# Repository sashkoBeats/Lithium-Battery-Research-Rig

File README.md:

# Lithium Battery Research Rig
University project development of a rig for 18650 lithium battery testing and research.   
End goal is an EV simulation rig for researching EV battery health and performance.   
Created by Aleksandar Zdravkov and Indra Erkens   
Fontys University of Applied Sciences   
S7 Project and CSA1/2 2022-2024

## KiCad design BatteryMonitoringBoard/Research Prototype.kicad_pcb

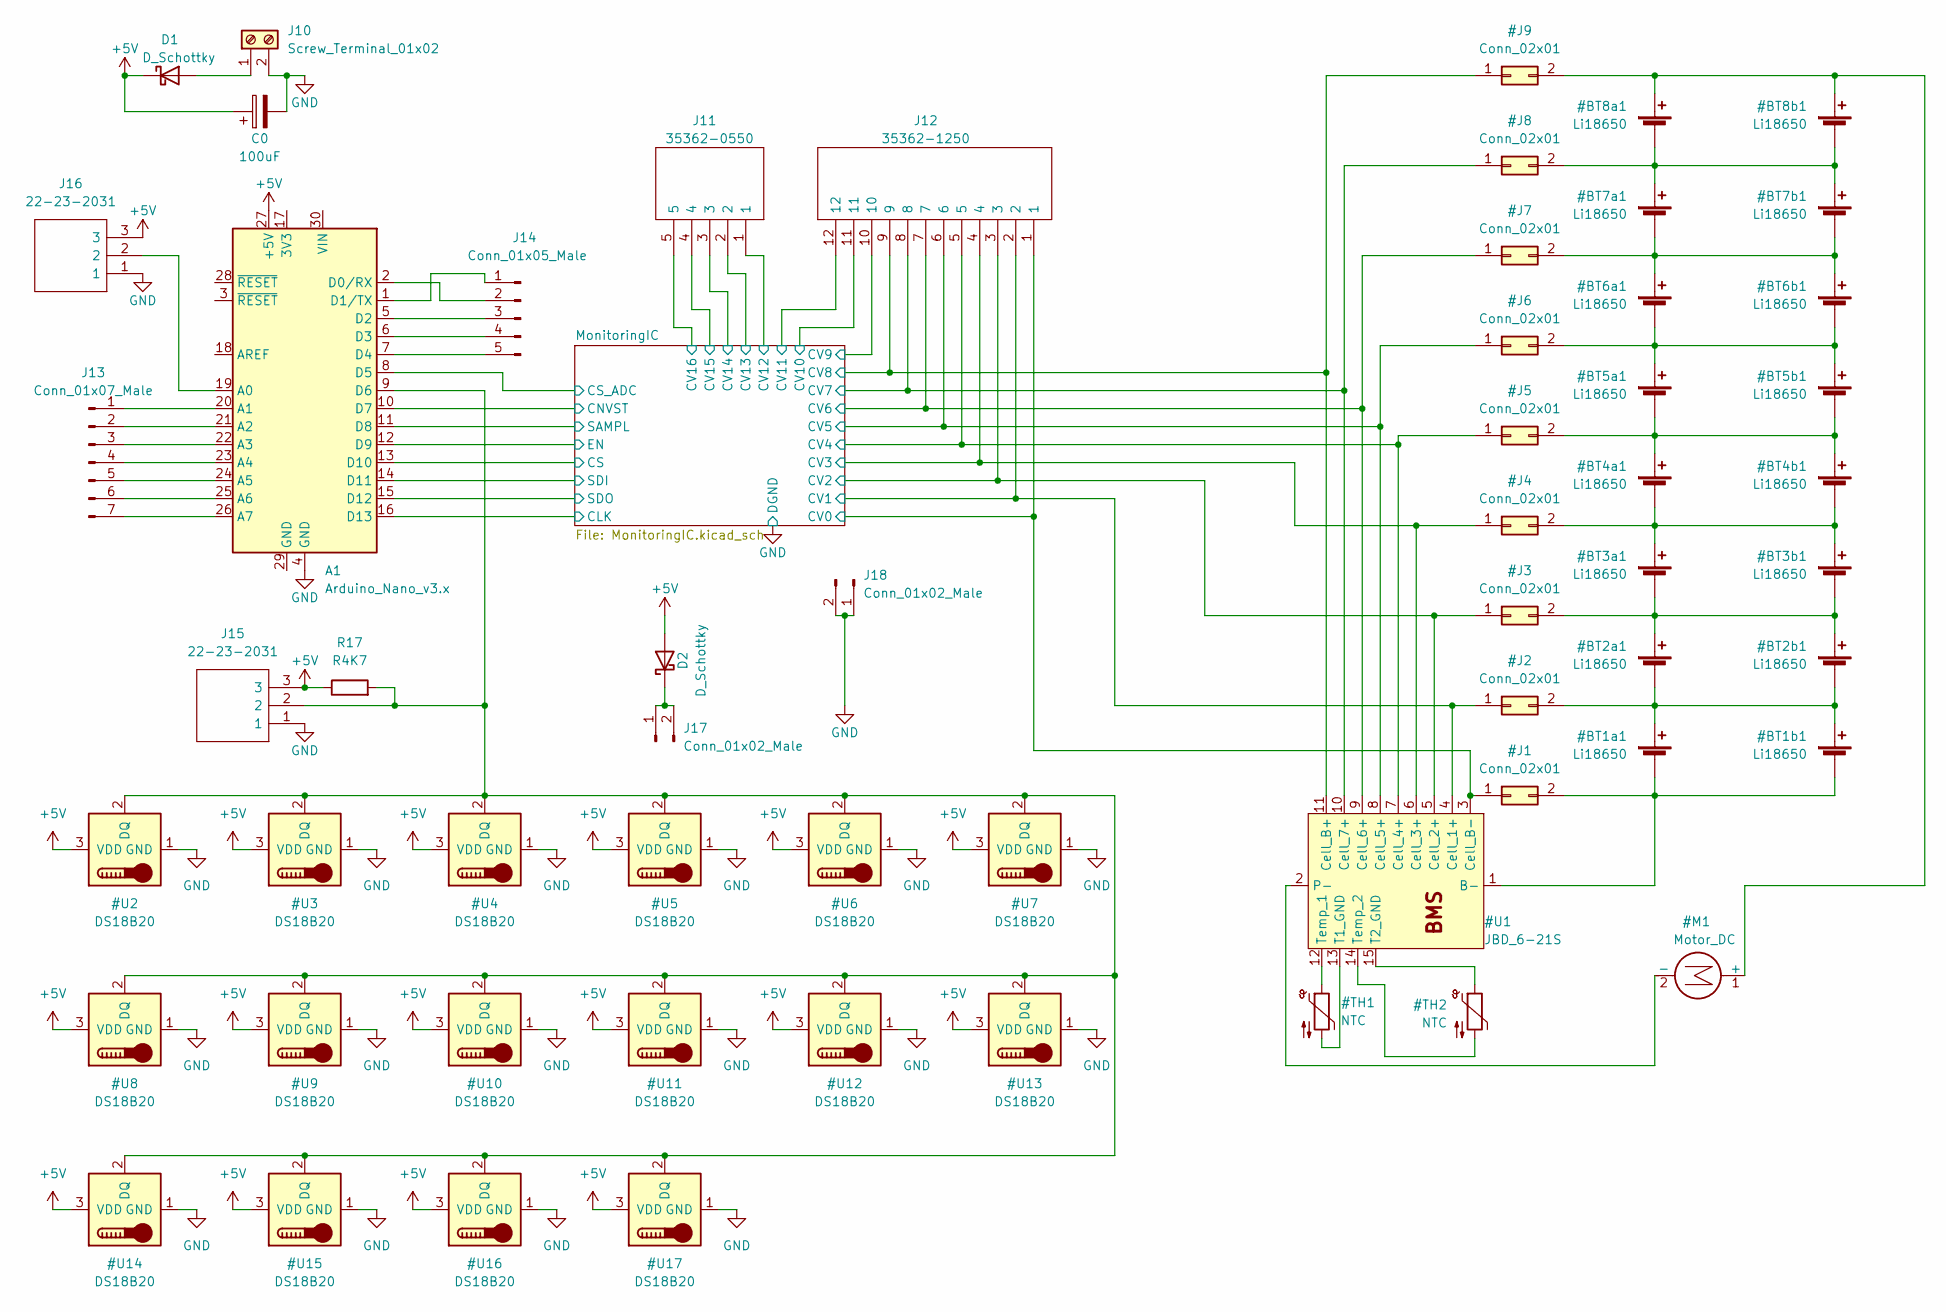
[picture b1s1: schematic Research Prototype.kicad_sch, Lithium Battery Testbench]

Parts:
A1: Arduino_Nano_v3.x; Arduino_Nano
C0: 100uF; CAPPRD250W50D680H1250
D1, D2: D_Schottky; SOD2512X115N
J10: Screw_Terminal_01x02; TerminalBlock_bornier-2_P5.08mm
J11: 35362-0550; SHDR5W50P0X200_1X5_1230X550X850P; Manufacturer_Part_Number 35362-0550; Mouser Part Number 538-35362-0550
J12: 35362-1250; 353621250; Manufacturer_Part_Number 35362-1250; Mouser Part Number 538-35362-1250
J13: Conn_01x07_Male; PinHeader_1x07_P2.54mm_Vertical
J14: Conn_01x05_Male
J15, J16: 22-23-2031; SHDR3W82P0X254_1X3_747X635X818P; Manufacturer_Part_Number 22-23-2031; Mouser Part Number 538-22-23-2031
J17, J18: Conn_01x02_Male; PinHeader_1x02_P2.54mm_Vertical
R17: R4K7; R_Axial_DIN0309_L9.0mm_D3.2mm_P12.70mm_Horizontal

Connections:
/MonitoringIC/CLK: A1.16 (D13); also elsewhere on the board
/MonitoringIC/CNVST: A1.10 (D7); also elsewhere on the board
/MonitoringIC/CS: A1.13 (D10); also elsewhere on the board
/MonitoringIC/CV9: J12.10; also elsewhere on the board
/MonitoringIC/CV10: J12.11; also elsewhere on the board
/MonitoringIC/CV11: J12.12; also elsewhere on the board
/MonitoringIC/CV12: J11.1; also elsewhere on the board
/MonitoringIC/CV13: J11.2; also elsewhere on the board
/MonitoringIC/CV14: J11.3; also elsewhere on the board
/MonitoringIC/CV15: J11.4; also elsewhere on the board
/MonitoringIC/CV16: J11.5; also elsewhere on the board
/MonitoringIC/EN: A1.12 (D9); also elsewhere on the board
/MonitoringIC/SAMPL: A1.11 (D8); also elsewhere on the board
/MonitoringIC/SDI: A1.14 (D11); also elsewhere on the board
/MonitoringIC/SDO: A1.15 (D12); also elsewhere on the board
unnamed: A1.1 (D1/TX), J14.1
unnamed: A1.2 (D0/RX), J14.2
unnamed: A1.5 (D2), J14.3
unnamed: A1.6 (D3), J14.4
unnamed: A1.7 (D4), J14.5
unnamed: A1.8 (D5), J14.6
unnamed: A1.19 (A0), J16.2
unnamed: A1.20 (A1), J13.1
unnamed: A1.21 (A2), J13.2
unnamed: A1.22 (A3), J13.3
unnamed: A1.23 (A4), J13.4
unnamed: A1.24 (A5), J13.5
unnamed: A1.25 (A6), J13.6
unnamed: A1.26 (A7), J13.7
unnamed: D1.2 (A), J10.1
unnamed: D2.1 (K), J17.1, J17.2

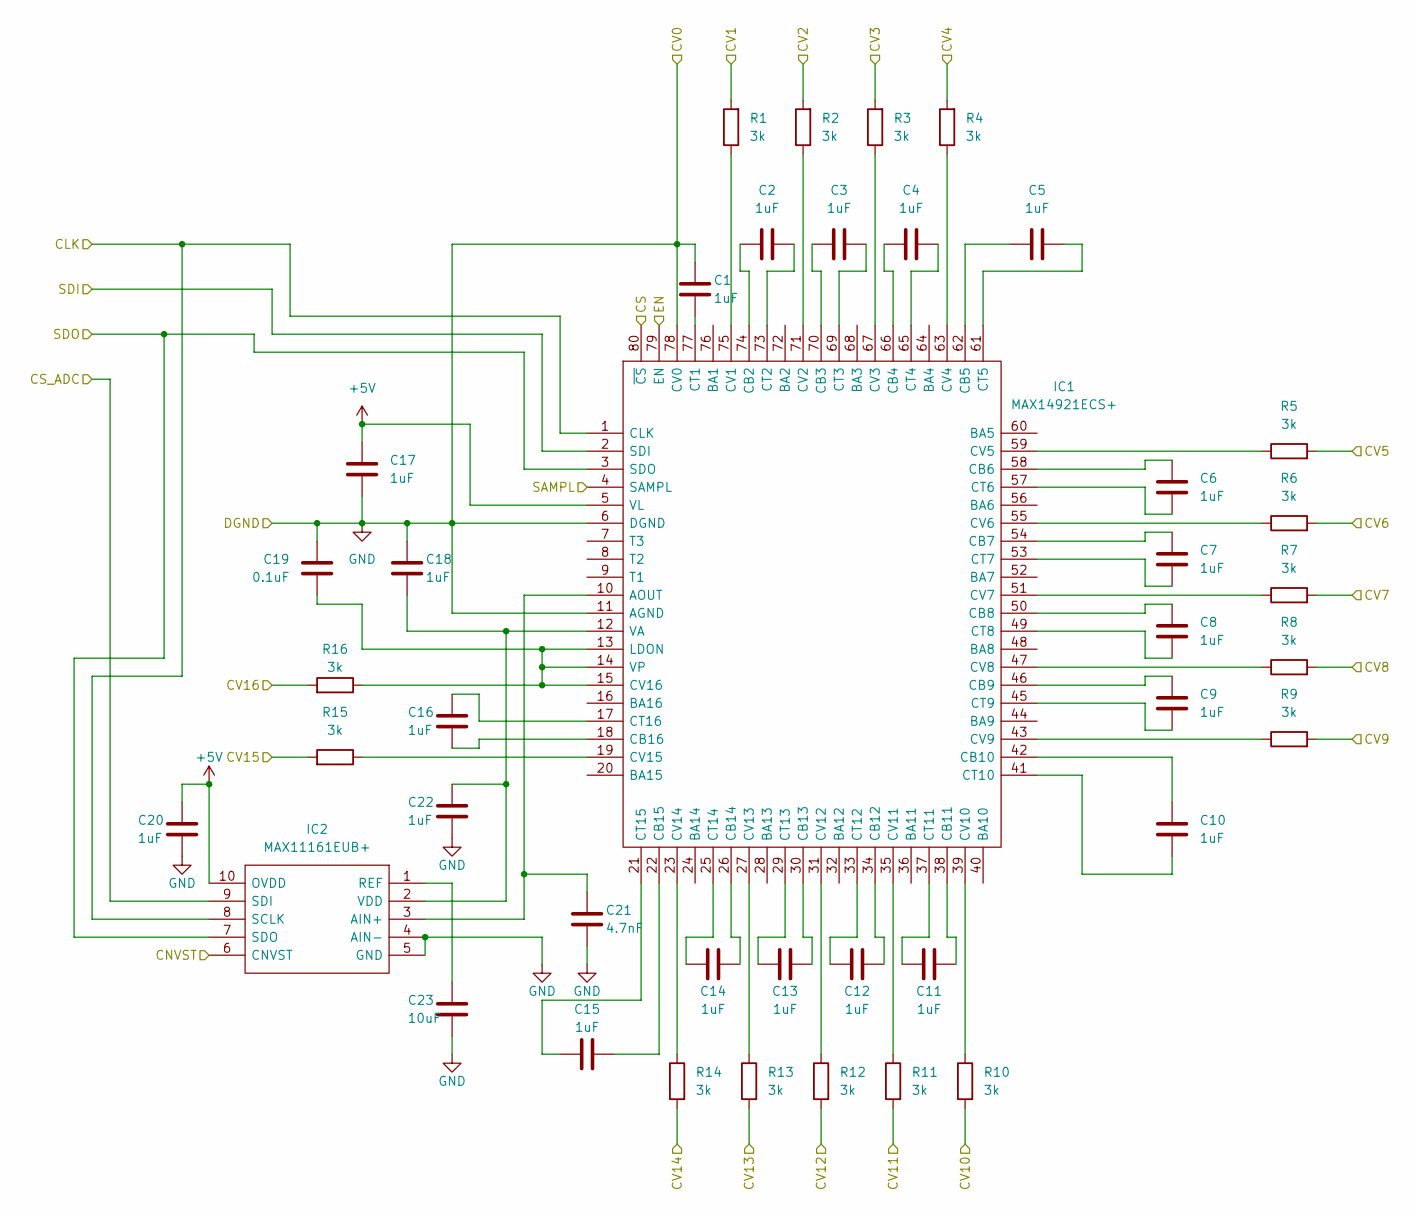
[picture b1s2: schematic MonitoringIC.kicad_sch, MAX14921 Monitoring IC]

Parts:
C1, C2, C3, C4, C5, C6, C7, C8, C9, C10, C11, C12, C13, C14, C15, C16, C17, C18, C20, C22: 1uF; CAPC3216X180N
C19: 0.1uF; CAPC1005X55N
C21: 4.7nF; CAPC1608X90N
C23: 10uF; CAPC2012X140N
IC1: MAX14921ECS+; QFP50P1400X1400X120-80N; Manufacturer_Part_Number MAX14921ECS+; Mouser Part Number 700-MAX14921ECS+
IC2: MAX11161EUB+; SOP50P490X110-10N; Manufacturer_Part_Number MAX11163EUB+; Mouser Part Number 700-MAX11163EUB+
R1, R2, R3, R4, R5, R6, R7, R8, R9, R10, R11, R12, R13, R14, R15, R16: 3k; ERJ3EK__0603_

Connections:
/MonitoringIC/CLK: IC1.1 (CLK), IC2.8 (SCLK); also elsewhere on the board
/MonitoringIC/CNVST: IC2.6 (CNVST); also elsewhere on the board
/MonitoringIC/CS: IC1.80 (~CS); also elsewhere on the board
/MonitoringIC/CV9: R9.2; also elsewhere on the board
/MonitoringIC/CV10: R10.2; also elsewhere on the board
/MonitoringIC/CV11: R11.2; also elsewhere on the board
/MonitoringIC/CV12: R12.2; also elsewhere on the board
/MonitoringIC/CV13: R13.2; also elsewhere on the board
/MonitoringIC/CV14: R14.2; also elsewhere on the board
/MonitoringIC/CV15: R15.2; also elsewhere on the board
/MonitoringIC/CV16: R16.2; also elsewhere on the board
/MonitoringIC/EN: IC1.79 (EN); also elsewhere on the board
/MonitoringIC/SAMPL: IC1.4 (SAMPL); also elsewhere on the board
/MonitoringIC/SDI: IC1.2 (SDI), IC2.9 (SDI); also elsewhere on the board
/MonitoringIC/SDO: IC1.3 (SDO), IC2.7 (SDO); also elsewhere on the board
unnamed: C1.2, IC1.77 (CT1)
unnamed: C2.1, IC1.73 (CT2)
unnamed: C2.2, IC1.74 (CB2)
unnamed: C3.1, IC1.69 (CT3)
unnamed: C3.2, IC1.70 (CB3)
unnamed: C4.1, IC1.65 (CT4)
unnamed: C4.2, IC1.66 (CB4)
unnamed: C5.1, IC1.61 (CT5)
unnamed: C5.2, IC1.62 (CB5)
unnamed: C6.1, IC1.58 (CB6)
unnamed: C6.2, IC1.57 (CT6)
unnamed: C7.1, IC1.54 (CB7)
unnamed: C7.2, IC1.53 (CT7)
unnamed: C8.1, IC1.50 (CB8)
unnamed: C8.2, IC1.49 (CT8)
unnamed: C9.1, IC1.46 (CB9)
unnamed: C9.2, IC1.45 (CT9)
unnamed: C10.1, IC1.42 (CB10)
unnamed: C10.2, IC1.41 (CT10)
unnamed: C11.1, IC1.37 (CT11)
unnamed: C11.2, IC1.38 (CB11)
unnamed: C12.1, IC1.34 (CB12)
unnamed: C12.2, IC1.33 (CT12)
unnamed: C13.1, IC1.30 (CB13)
unnamed: C13.2, IC1.29 (CT13)
unnamed: C14.1, IC1.26 (CB14)
unnamed: C14.2, IC1.25 (CT14)
unnamed: C15.1, IC1.21 (CT15)
unnamed: C15.2, IC1.22 (CB15)
unnamed: C16.1, IC1.17 (CT16)
unnamed: C16.2, IC1.18 (CB16)
unnamed: C18.2, C22.1, IC1.12 (VA), IC2.2 (VDD)
unnamed: C19.1, IC1.13 (LDON), IC1.14 (VP), IC1.15 (CV16), R16.1
unnamed: C21.1, IC1.10 (AOUT), IC2.3 (AIN+)
unnamed: C23.1, IC2.1 (REF)
unnamed: IC1.19 (CV15), R15.1
unnamed: IC1.23 (CV14), R14.1
unnamed: IC1.27 (CV13), R13.1
unnamed: IC1.31 (CV12), R12.1
unnamed: IC1.35 (CV11), R11.1
unnamed: IC1.39 (CV10), R10.1
unnamed: IC1.43 (CV9), R9.1
unnamed: IC1.47 (CV8), R8.1
unnamed: IC1.51 (CV7), R7.1
unnamed: IC1.55 (CV6), R6.1
unnamed: IC1.59 (CV5), R5.1
unnamed: IC1.63 (CV4), R4.1
unnamed: IC1.67 (CV3), R3.1
unnamed: IC1.71 (CV2), R2.1
unnamed: IC1.75 (CV1), R1.1

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
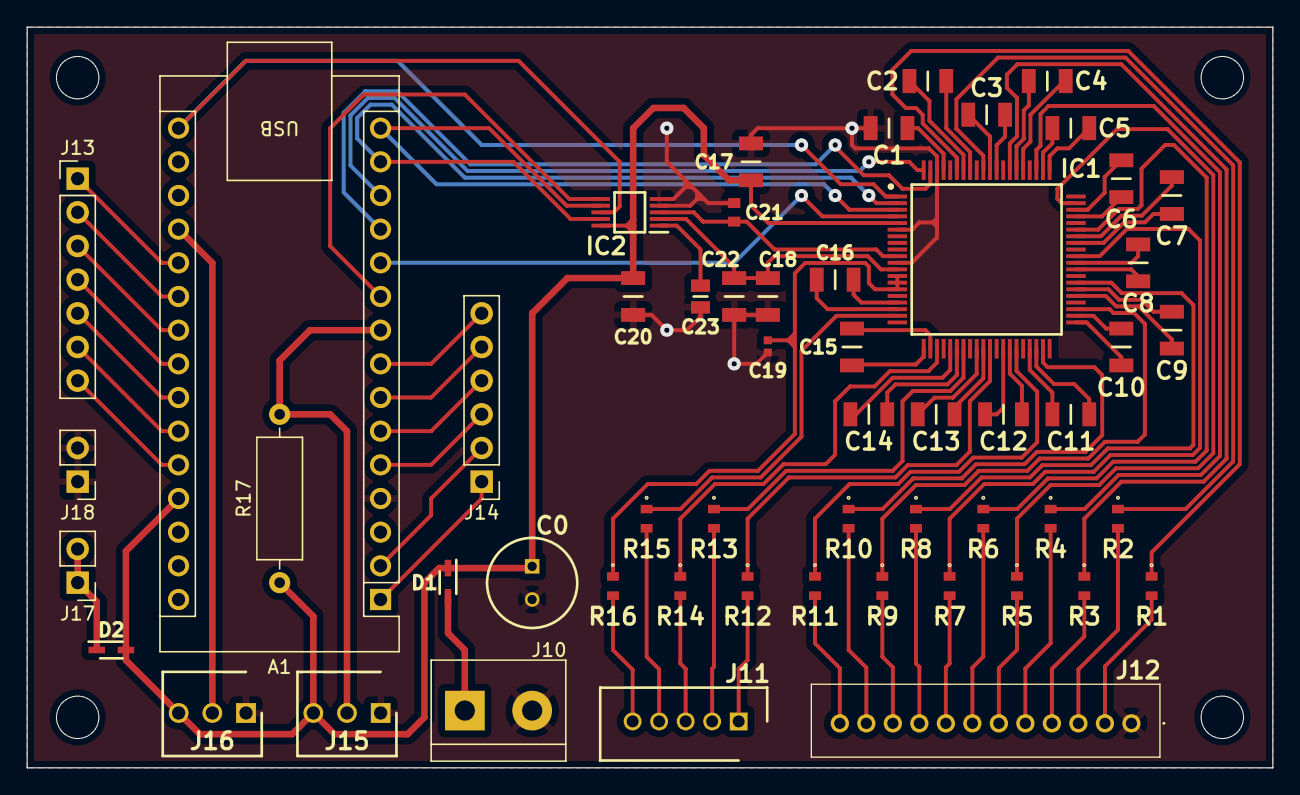
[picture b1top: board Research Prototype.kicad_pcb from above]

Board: 2 copper layers, 94.0 x 55.9 mm, 55 parts (0 on the bottom side), 92 nets.

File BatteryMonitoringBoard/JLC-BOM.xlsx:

Comment | Designator | Footprint | JLCPCB Part #（optional）
100uF | C0 | CAPPRD250W50D680H1250 | C109392
1uF | C1, C2, C3, C4, C5, C6, C7, C8, C9, C10, C11, C12, C13, C14, C15, C16, C17, C18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 | CAPC3216X180N | C13832
0.1uF | C19 | CAPC1005X55N | C1525
4.7nF | C21 | CAPC1608X90N | C85980
10uF | C23 | CAPC2012X140N | C1713
D_Schottky | D1, D2 | SOD2512X115N | C435857
MAX14921ECS+ | IC1 | QFP50P1400X1400X120-80N | C2932577
3k | R1, R2, R3, R4, R5, R6, R7, R8, R9, R10, R11, R12, R13, R14, R15, R16 | ERJ3EK__0603_ | C278616

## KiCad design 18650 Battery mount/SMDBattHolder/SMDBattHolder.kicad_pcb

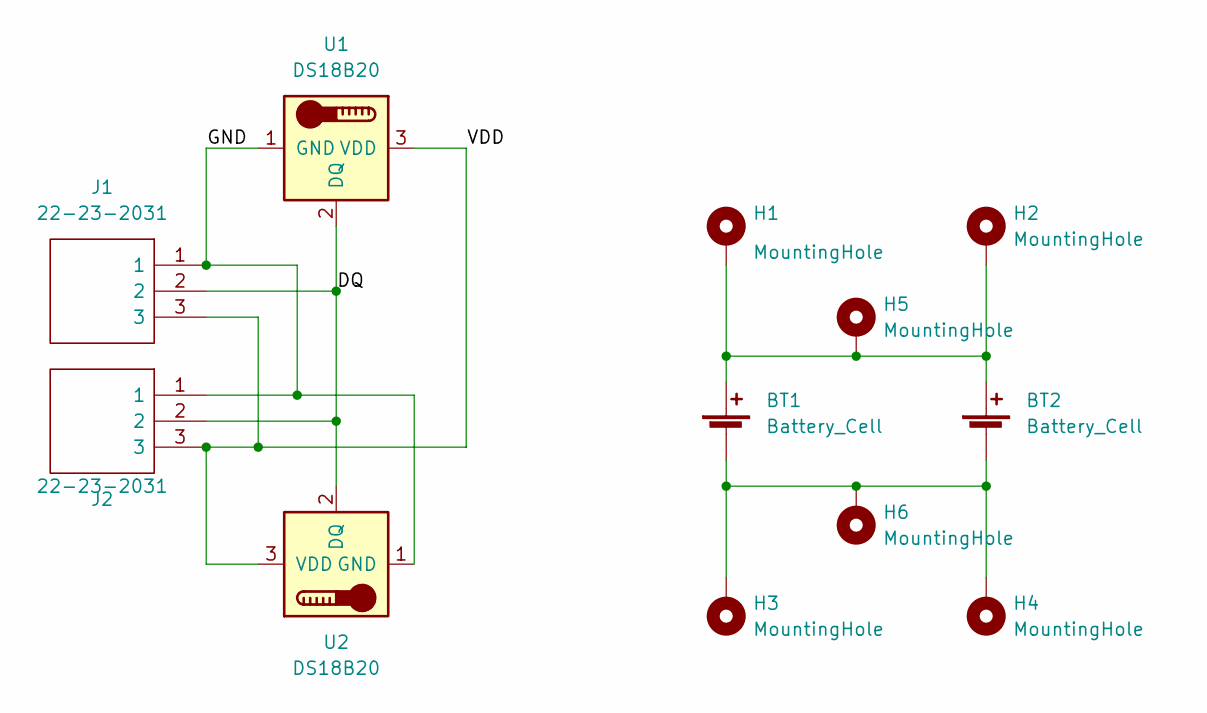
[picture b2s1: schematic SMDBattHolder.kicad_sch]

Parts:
BT1, BT2: Battery_Cell; ElBatterinoMounterino
H1, H2, H3, H4: MountingHole; MountingHole_3.2mm_M3_Pad_TopOnly
H5, H6: MountingHole; Long Long Pad
J1, J2: 22-23-2031; SHDR3W82P0X254_1X3_747X635X818P; Manufacturer_Part_Number 22-23-2031; Mouser Part Number 538-22-23-2031
U1, U2: DS18B20; TO-92_Inline

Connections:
/DQ: J1.2, J2.2, U1.2 (DQ), U2.2 (DQ)
/GND: J1.1, J2.1, U1.1 (GND), U2.1 (GND)
/VDD: J1.3, J2.3, U1.3 (VDD), U2.3 (VDD)
unnamed: BT1.1 (+), BT2.1 (+), H1.1, H2.1, H5.1
unnamed: BT1.2 (-), BT2.2 (-), H3.1, H4.1, H6.1

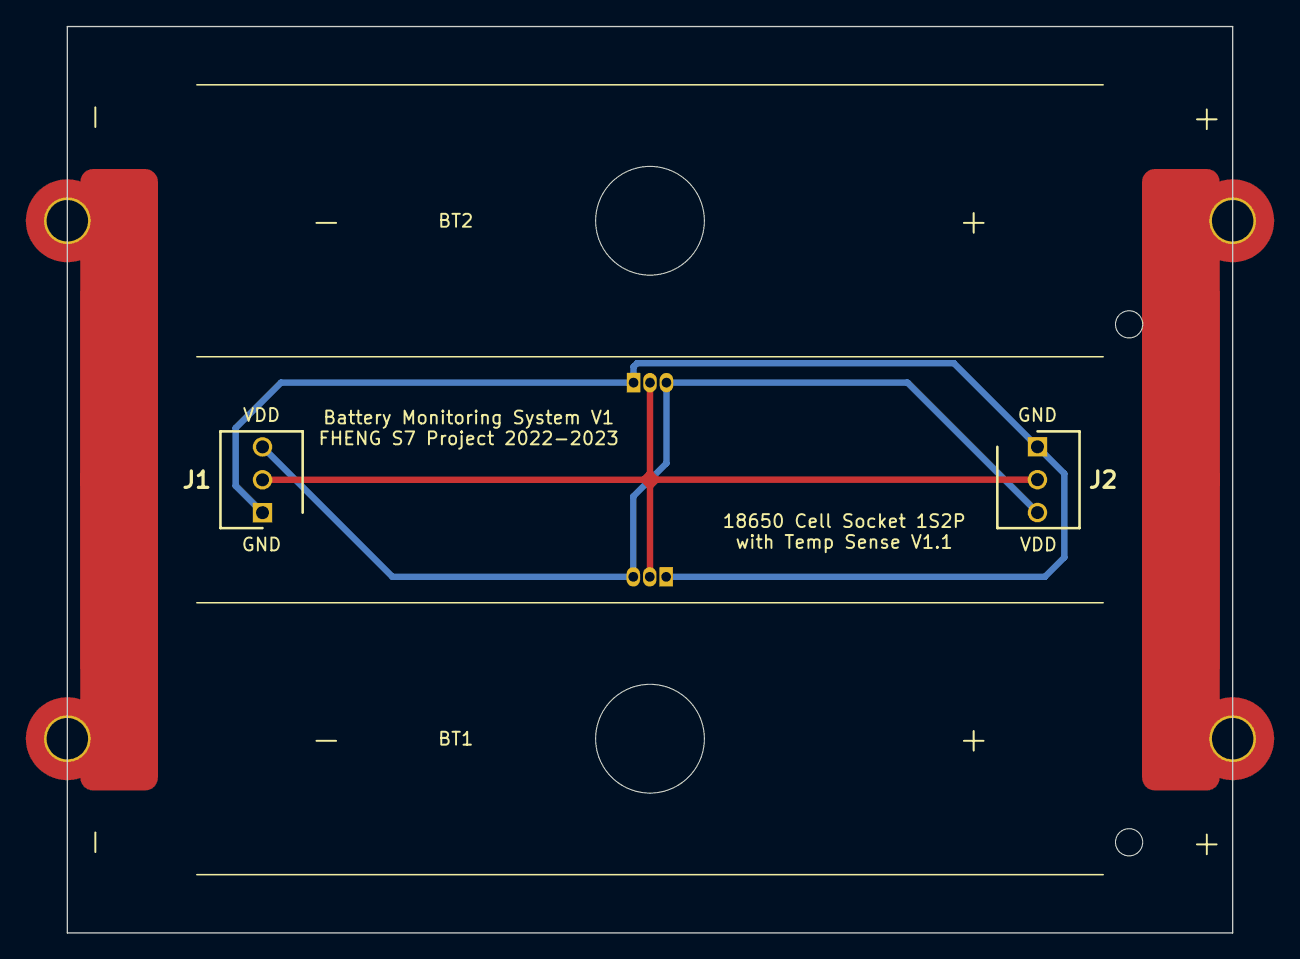
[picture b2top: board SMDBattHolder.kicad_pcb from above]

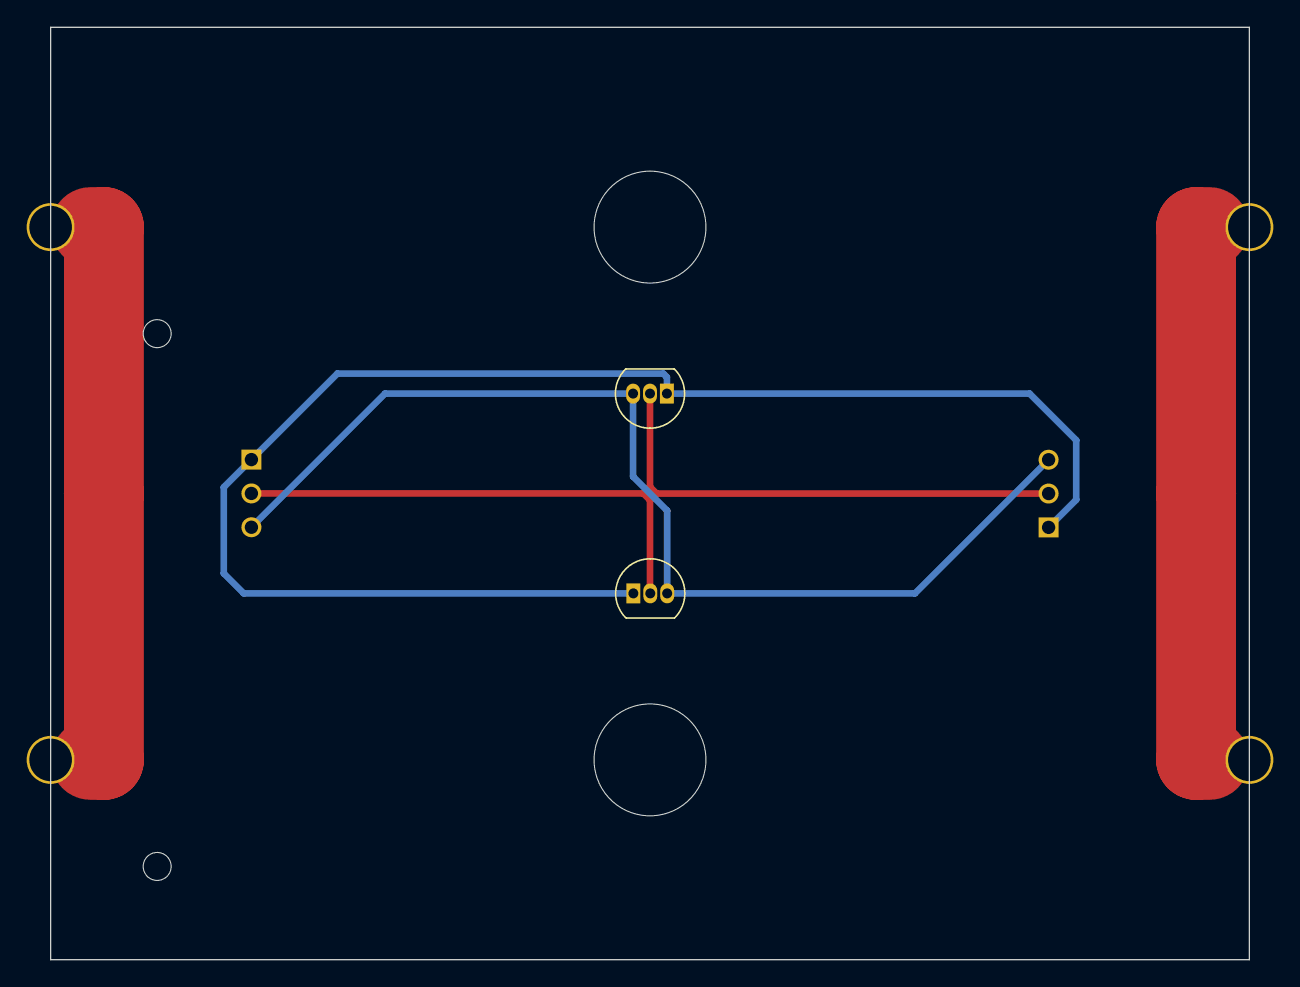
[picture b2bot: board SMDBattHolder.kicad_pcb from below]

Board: 2 copper layers, 90.0 x 70.0 mm, 12 parts (2 on the bottom side), 5 nets.

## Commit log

2024-07-15 Initial commit 18650 Battery Mount
2024-07-15 Initial commit Arduino code
2024-07-15 Initial commit Battery Monitoring board
2024-07-15 Initial commit Battery Monitor PC
2024-07-15 Initial commit CAD files
2024-07-15 Initial commit CAD files part 2
2024-07-15 Initial commit CAD files part 3
2024-07-15 Initial commit Docs
2024-07-15 Initial commit JBD BMS files
2024-07-15 Initial commit Media
2024-07-15 Initial commit Media part 2
2024-07-17 Added User Guide R1
